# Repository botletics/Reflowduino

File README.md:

# Reflowduino

## Introduction
First off, let's briefly explain a circuit board is assembled. To aid in the explanation, let's take the analogy of baking a pizza. First of all you'll need the crust, which for us is a bare printed circuit board (PCB) made with different layers of a plastic substrate and copper traces that make the electrical connections. Next, we'll need the cheese that holds everything together, which for us is solder paste (yes, solder in the form of a paste) which "reflows" (solidifies or cures) at a high temperature. The solder paste is applied to the exposed copper pads on the PCB by way of a stencil that is aligned over the PCB. Then we'll grab some toppings, the electrical components, and place them in their appropriate locations on top of the solder paste. The final step is to bake our "pizza" so that the "cheese" holds all the components in place to yield our final assembled board! This is where the Reflowduino project comes in...

## Overview
The Reflowduino project is an entire do-it-yourself (DIY) reflow ecosystem consisting of open-source hardware specifically built to make it easy to control reflow appliances and apply PID temperature control while maintaining full flexibility in programming and usage while offering a bunch of features.

Since I'm a firm believer of great online resources having learned everything on my own aside from my Mechanical Engineering degree, I'm sharing all of this as completely open-source for everyone to enjoy, including EAGLE PCB files, Arduino IDE example code, sample Android app for Bluetooth control, and full tutorials on how to modify a toaster oven to start cookin’!

That being said, I do offer the boards listed below [for sale on my website](https://www.botletics.com/products/). Each order helps me out a little bit in creating and sharing new projects with everyone! :)

## Resources
Don’t forget to check out the [comprehensive Github wiki](https://github.com/botletics/Reflowdiuno/wiki)!
I also posted [this Instructable](https://www.instructables.com/id/Reflowduino-DIY-BLE-Reflow-Oven-Controller/) as a quick 'n dirty summary of everything here as well as on [Hackster.io](https://www.hackster.io/botletics/diy-reflow-oven-with-reflowduino-af0219)!

All PCB design files and hardware are released under the [Creative Commons Attribution Share Alike 4.0](https://choosealicense.com/licenses/cc-by-sa-4.0/) license.

All other software is released under the [GNU General Public License v3.0](https://choosealicense.com/licenses/gpl-3.0/).

## Safety Disclaimer
If you are a beginner in electronics or don't have the proper experience to work with mains voltage, I would suggest that you either don't mess with it, consult a professional, or keep learning until you're proficient enough! I am not liable for any mishaps that may occur due to misuse of the Reflowduino or its associated components or electrical system (including mains power). Take all safety precautions as necessary, such as gloves and certified safety glasses. Moreover, it is not recommended that you use the same appliance to reflow PCB's and also to cook food for consumption, which may result in food poisoning, especially with leaded solder. You are fully responsible for your actions, and perform them at your own risk!

That being said, DIY away my friends... have fun and stay safe!

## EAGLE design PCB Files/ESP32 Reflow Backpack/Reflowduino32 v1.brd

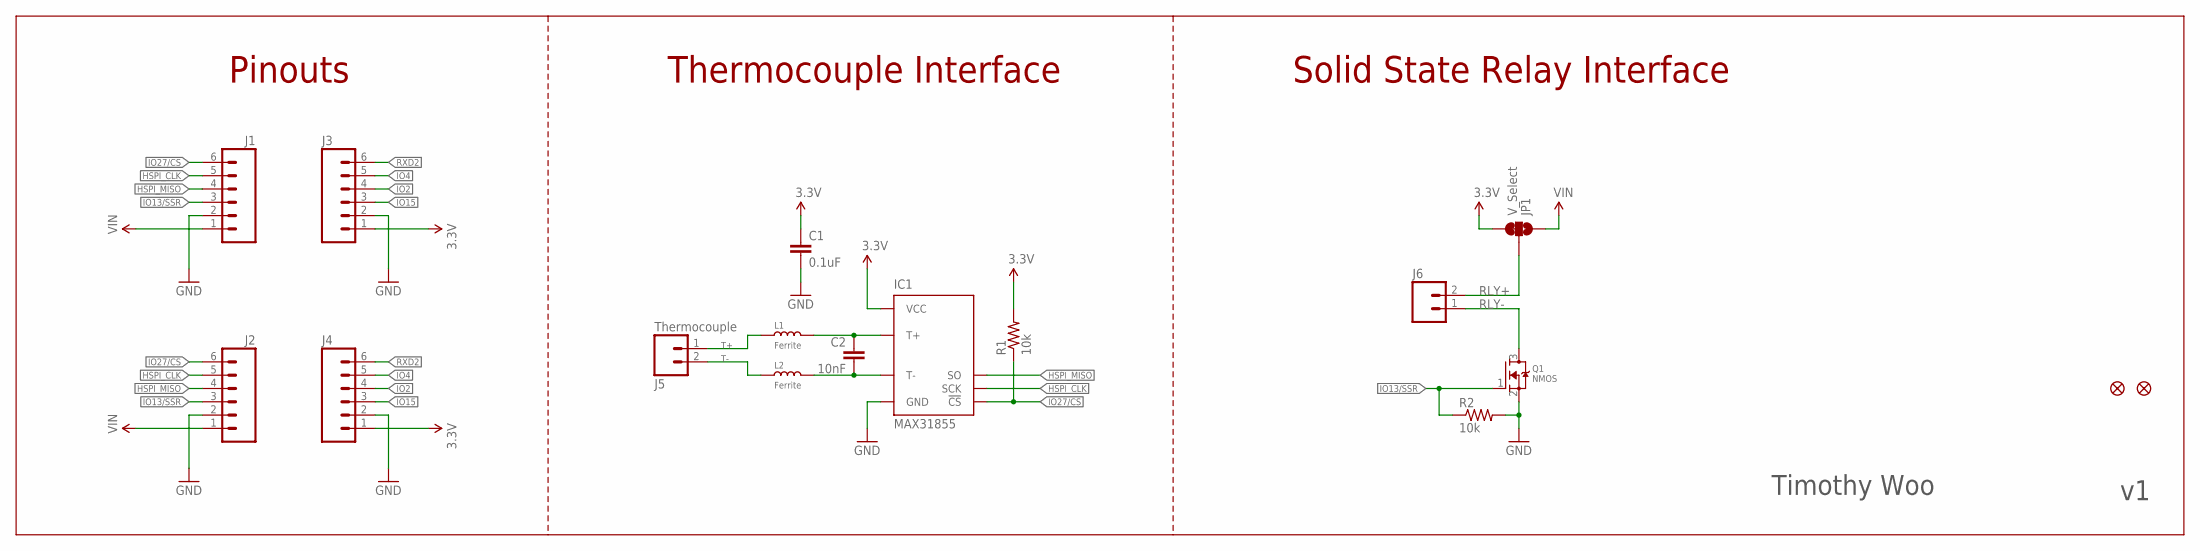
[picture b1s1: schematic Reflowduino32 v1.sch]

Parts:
C1: 0.1uF; 0603-CAP-MARKED
C2: 10nF; 0603-CAP-MARKED
FID1, FID2: FIDUCIAL; FIDUCIAL_1MM
IC1: MAX31855; MAX31855_SOIC8
J1, J3: M06SILK_PTH; 1X06
J2, J4: M06NO_SILK_FEMALE_PTH; 1X06_NO_SILK
J5: Thermocouple; SCREWTERMINAL-3.5MM-2
J6: M023.5MM; SCREWTERMINAL-3.5MM-2
JP1: V_Select; SMT-JUMPER_3_1-NC_TRACE_SILK
L1, L2: Ferrite; L0603
Q1: NMOS; SOT23-3
R1, R2: 10k; 0603-RES-MARKED

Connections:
3.3V: C1.1, IC1.4 (VCC), J3.1, J4.1, JP1.3, R1.2
GND: C1.2, IC1.1 (GND), J1.2, J2.2, J3.2, J4.2, Q1.2 (S), R2.2
HSPI_CLK: IC1.5 (SCK), J1.5, J2.5
HSPI_MISO: IC1.7 (SO), J1.4, J2.4
IO2: J3.4, J4.4
IO4: J3.5, J4.5
IO13/SSR: J1.3, J2.3, Q1.1 (G), R2.1
IO15: J3.3, J4.3
IO27/CS: IC1.6 (!CS), J1.6, J2.6, R1.1
unnamed: C2.2, IC1.2 (T-), L2.2
unnamed: C2.1, IC1.3 (T+), L1.2
RLY+: J6.2, JP1.2
RLY-: J6.1, Q1.3 (D)
RXD2: J3.6, J4.6
T+: J5.1, L1.1
T-: J5.2, L2.1
VIN: J1.1, J2.1, JP1.1

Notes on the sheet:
Thermocouple Interface
Solid State Relay Interface
Pinouts
Timothy Woo

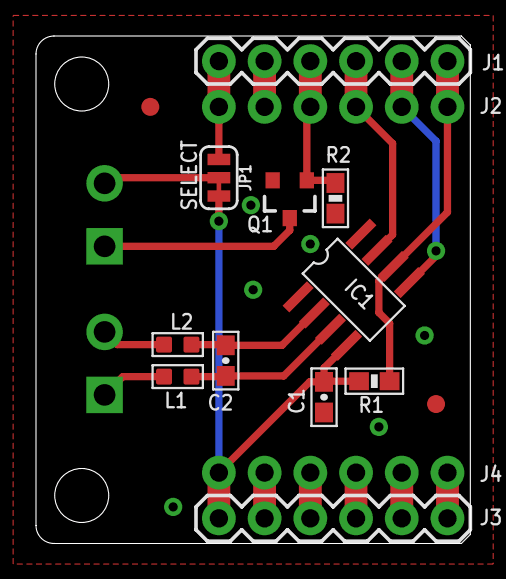
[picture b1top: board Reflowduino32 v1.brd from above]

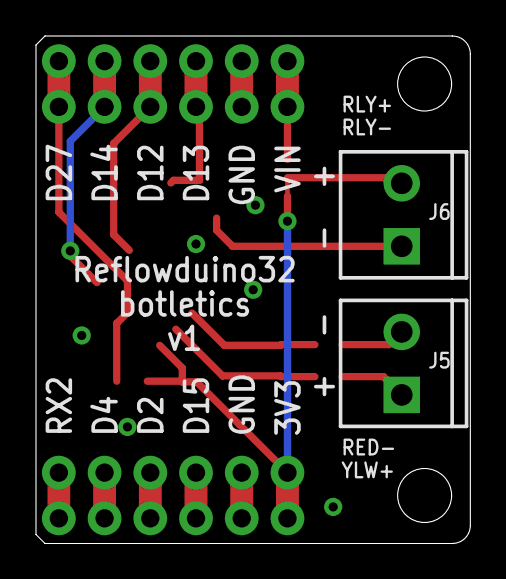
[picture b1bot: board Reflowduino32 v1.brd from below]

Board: 2 copper layers, 24.1 x 28.2 mm, 17 parts (2 on the bottom side), 17 nets.

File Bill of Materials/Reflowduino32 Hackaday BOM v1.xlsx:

Part # | Part Name | Quantity | Notes | Mfg. Number
C1 | 0.1uF/16V/20%/X7R Ceramic Capacitor 0603 | 1 |  | CL10B104MO8NNND
C2 | 0.01uF/16V/10%/X7R Ceramic Capacitor 0603 | 1 |  | CL10B103KO8NNNC
IC1 | MAX31855 Thermocouple-to-Digital Converter | 1 | K-type | MAX31855KASA+
J1, J3 | 1x6 Female Header, 2.54mm Pitch/8.5mm Tall | 2
J5-J6 | 2-pin Screw Terminal Block, 3.5mm Pitch | 2 |  | T502015000J0G
L1-L2 | 600Ohm Ferrite Bead, Signal Filter, 0603 | 2 |  | BLM18TG601TN1D
Q1 | N-MOSFET, 200mA, SOT23-3 | 1 | Very low Vth | BSS138L
R1-R2 | 10k/5%/0.1W Resistor 0603 | 2 |  | NRC06J103TRF

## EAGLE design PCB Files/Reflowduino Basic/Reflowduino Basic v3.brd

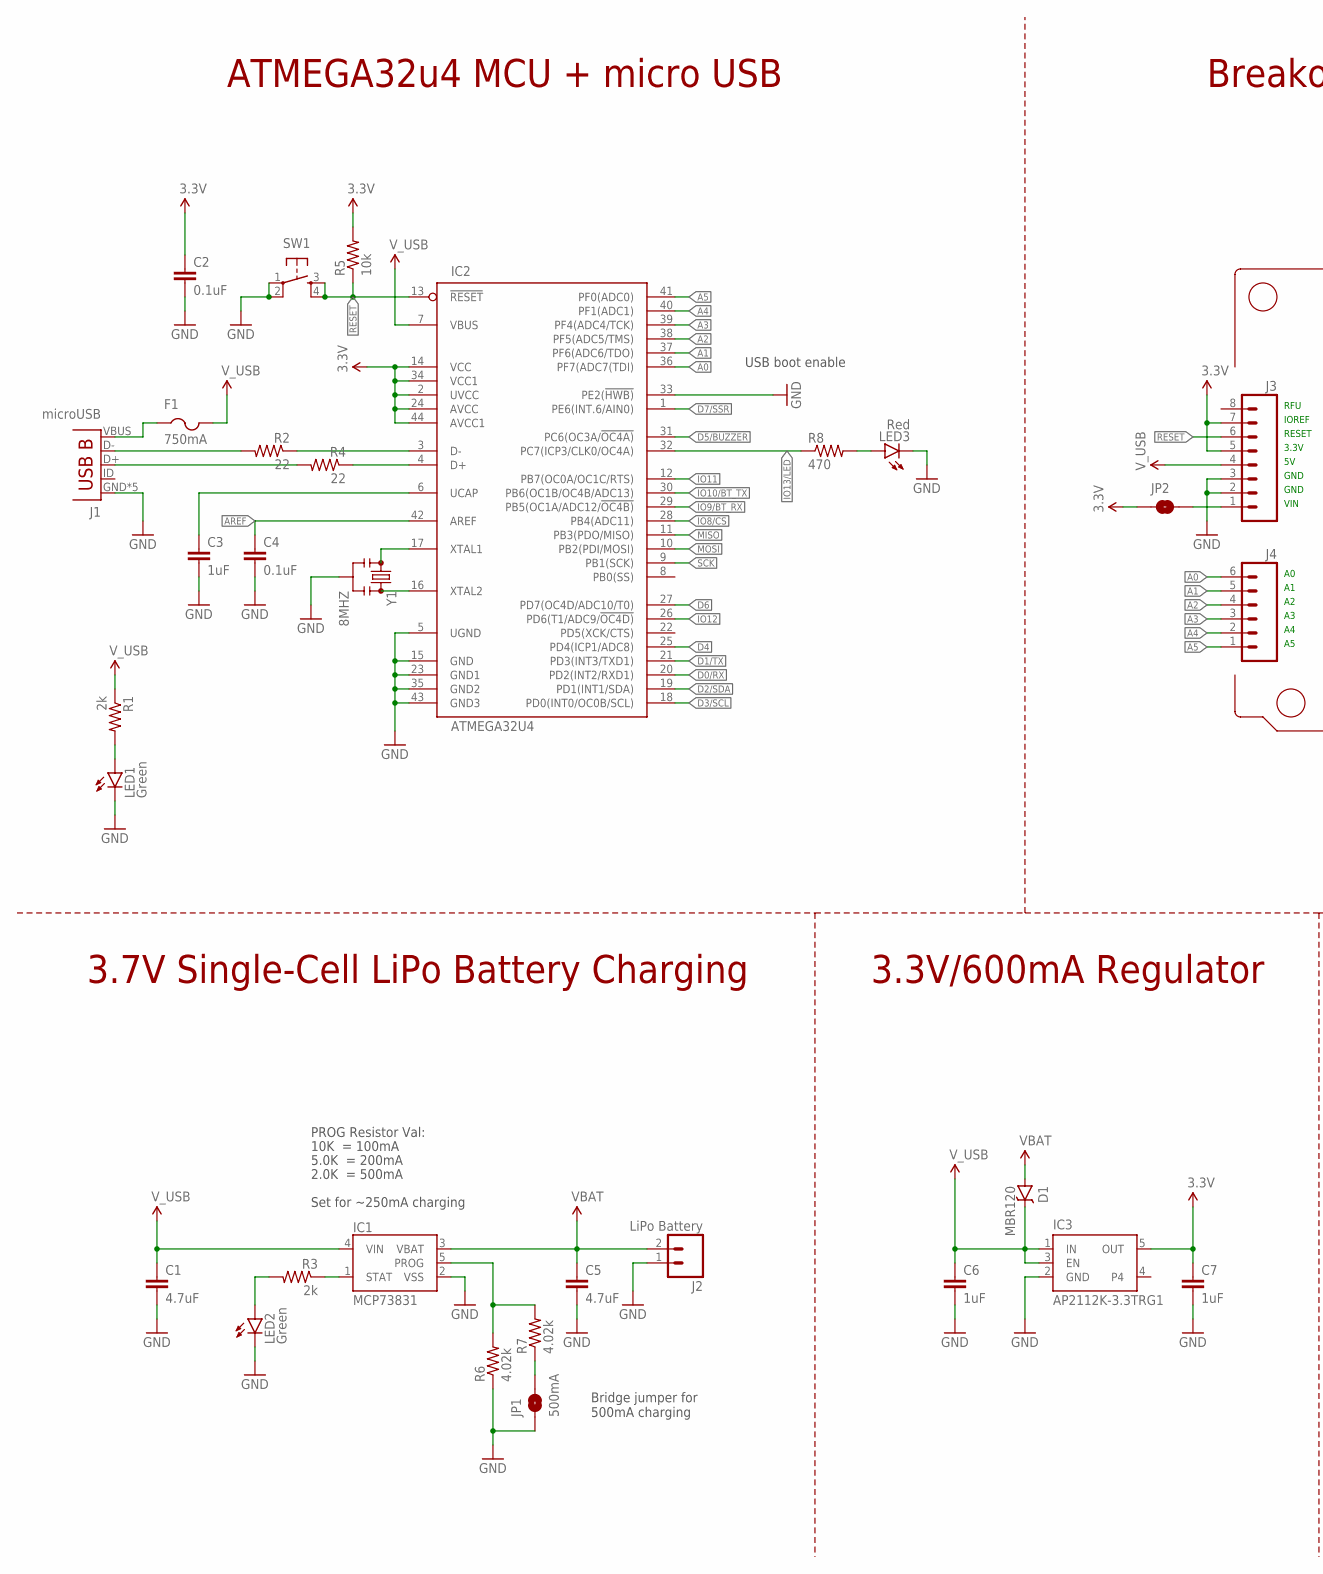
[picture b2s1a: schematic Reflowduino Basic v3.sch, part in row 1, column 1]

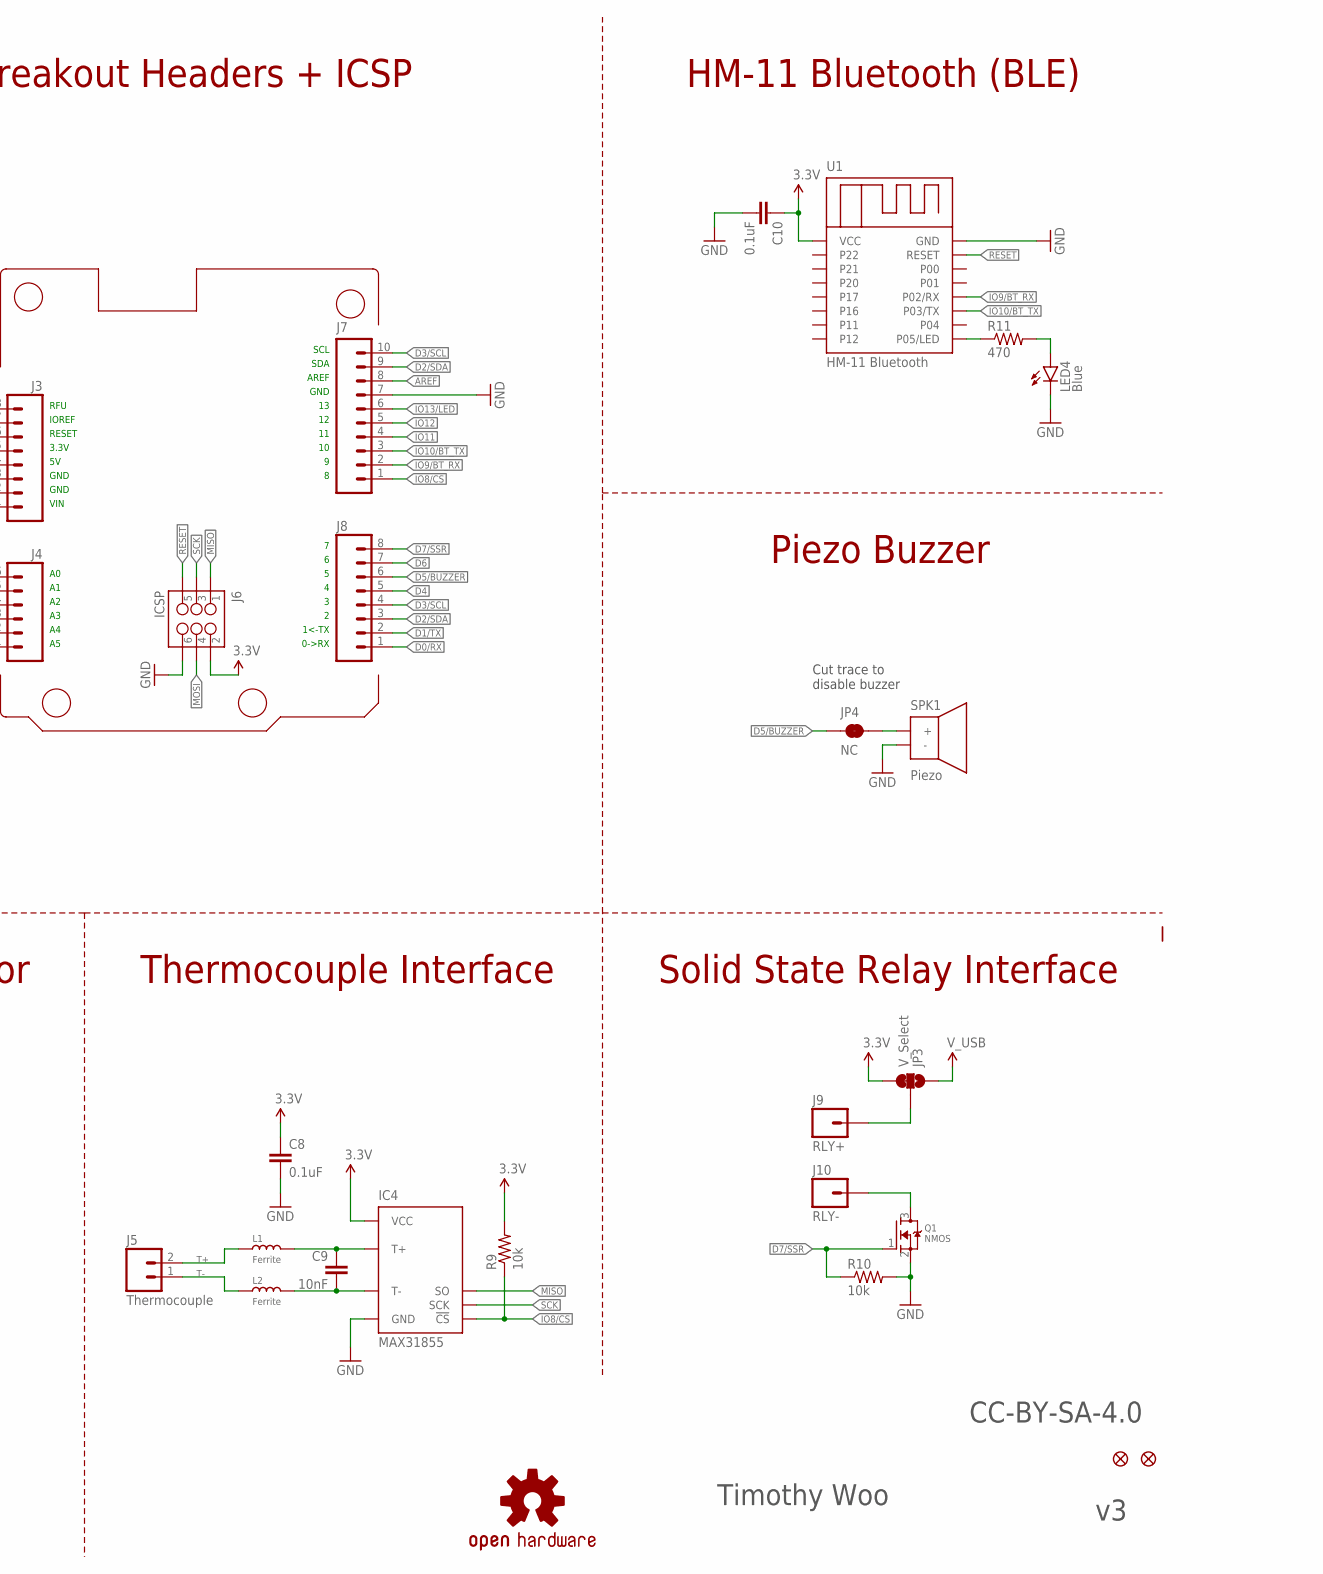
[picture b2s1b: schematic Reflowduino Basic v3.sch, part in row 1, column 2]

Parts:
C1, C5: 4.7uF; 0603-CAP-MARKED
C2, C4, C8, C10: 0.1uF; 0603-CAP-MARKED
C3, C6, C7: 1uF; 0603-CAP-MARKED
C9: 10nF; 0603-CAP-MARKED
D1: MBR120; SOD-123FL
F1: 750mA; 1210
FID1, FID2: FIDUCIAL; FIDUCIAL_1MM
IC1: MCP73831; SOT23-5
IC2: ATMEGA32U4; TQFP44
IC3: AP2112K-3.3TRG1; SOT23-5
IC4: MAX31855; MAX31855_SOIC8
J1: microUSB; USB-B-MICRO-SMD
J2: LiPo Battery; JST-2-SMD
J3, J8: M08SILK_PTH; 1X08
J4: M06SILK_PTH; 1X06
J5: Thermocouple; SCREWTERMINAL-3.5MM-2
J6: ICSP; 2X3
J7: M10SILK_PTH; 1X10
J9: RLY+; 1X01_LONGPAD
J10: RLY-; 1X01_LONGPAD
JP1: 500mA; SMT-JUMPER_2_NO_SILK
JP2: JUMPER-SMT_2_NO_SILK; SMT-JUMPER_2_NO_SILK
JP3: V_Select; SMT-JUMPER_3_1-NC_TRACE_SILK
JP4: NC; SMT-JUMPER_2_NC_TRACE_SILK
L1, L2: Ferrite; L0603
LED1, LED2: Green; LED-0603-MARKED
LED3: Red; LED-0603-MARKED
LED4: Blue; LED-0603-MARKED
LOGO1: OSHW-LOGOL; OSHW-LOGO-L
Q1: NMOS; SOT23-3
R1, R3: 2k; 0603-RES-MARKED
R2, R4: 22; 0603-RES-MARKED
R5, R9, R10: 10k; 0603-RES-MARKED
R6, R7: 4.02k; 0603-RES-MARKED
R8, R11: 470; 0603-RES-MARKED
SPK1: Piezo; BUZZER_PKMCS0909E4000
SW1: SWITCH_MOMENTARY_SPST_4-PINRECT; TACTILE_SWITCH_SMD_4.6X2.8MM
U1: HM-11 Bluetooth; JDY-08_BLUETOOTH
Y1: 8MHZ; CSTCE_RESONATOR_SMD

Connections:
3.3V: C2.1, C7.1, C8.1, C10.1, IC2.2 (UVCC), IC2.14 (VCC), IC2.24 (AVCC), IC2.34 (VCC1), IC2.44 (AVCC1), IC3.5 (OUT), IC4.4 (VCC), J3.5, J3.7, J6.2, JP2.1, JP3.3, R5.2, R9.2, U1.1 (VCC)
A0: IC2.36 (PF7(ADC7(TDI)), J4.6
A1: IC2.37 (PF6(ADC6/TDO)), J4.5
A2: IC2.38 (PF5(ADC5/TMS)), J4.4
A3: IC2.39 (PF4(ADC4/TCK)), J4.3
A4: IC2.40 (PF1(ADC1)), J4.2
A5: IC2.41 (PF0(ADC0)), J4.1
AREF: C4.1, IC2.42 (AREF), J7.8
D0/RX: IC2.20 (PD2(INT2/RXD1)), J8.1
D1/TX: IC2.21 (PD3(INT3/TXD1)), J8.2
D2/SDA: IC2.19 (PD1(INT1/SDA)), J7.9, J8.3
D3/SCL: IC2.18 (PD0(INT0/OC0B/SCL)), J7.10, J8.4
D4: IC2.25 (PD4(ICP1/ADC8)), J8.5
D5/BUZZER: IC2.31 (PC6(OC3A/!OC4A)), J8.6, JP4.1
D6: IC2.27 (PD7(OC4D/ADC10/T0)), J8.7
D7/SSR: IC2.1 (PE6(INT.6/AIN0)), J8.8, Q1.1 (G), R10.1
D+: IC2.4 (D+), R4.1
D-: IC2.3 (D-), R2.1
DC+: J9.1, JP3.2
DC-: J10.1, Q1.3 (D)
GND: C1.2, C2.2, C3.2, C4.2, C5.2, C6.2, C7.2, C8.2, C10.2, IC1.2 (VSS), IC2.5 (UGND), IC2.15 (GND), IC2.23 (GND1), IC2.33 (PE2(!HWB)), IC2.35 (GND2), IC2.43 (GND3), IC3.2 (GND), IC4.1 (GND), J1.GND, J1.SHIELD1 (GND), J1.SHIELD2 (GND), J1.SHIELD3 (GND), J1.SHIELD4 (GND), J2.1 (2), J3.2, J3.3, J6.6, J7.7, JP1.1, LED1.C, LED2.C, LED3.C, LED4.C, Q1.2 (S), R6.1, R10.2, SPK1.2 (-), SW1.1, SW1.2, U1.16 (GND), Y1.2
IO8/CS: IC2.28 (PB4(ADC11)), IC4.6 (!CS), J7.1, R9.1
IO9/BT_RX: IC2.29 (PB5(OC1A/ADC12/!OC4B)), J7.2, U1.12 (P02/RX)
IO10/BT_TX: IC2.30 (PB6(OC1B/OC4B/ADC13)), J7.3, U1.11 (P03/TX)
IO11: IC2.12 (PB7(OC0A/OC1C/RTS)), J7.4
IO12: IC2.26 (PD6(T1/ADC9/!OC4D)), J7.5
IO13/LED: IC2.32 (PC7(ICP3/CLK0/OC4A)), J7.6, R8.1
LED: R11.1, U1.9 (P05/LED)
MISO: IC2.11 (PB3(PDO/MISO)), IC4.7 (SO), J6.1
MOSI: IC2.10 (PB2(PDI/MOSI)), J6.4
unnamed: IC2.17 (XTAL1), Y1.1
unnamed: J1.D-, R2.2
unnamed: J1.D+, R4.2
unnamed: JP4.2, SPK1.1 (+)
unnamed: LED2.A, R3.2
unnamed: C9.2, IC4.2 (T-), L2.2
unnamed: C9.1, IC4.3 (T+), L1.2
unnamed: LED1.A, R1.2
unnamed: IC2.16 (XTAL2), Y1.3
unnamed: LED4.A, R11.2
unnamed: JP1.2, R7.1
unnamed: J3.1, JP2.2
unnamed: LED3.A, R8.2
PROG: IC1.5 (PROG), R6.2, R7.2
RESET: IC2.13 (!RESET), J3.6, J6.5, R5.1, SW1.3, SW1.4, U1.15 (RESET)
SCK: IC2.9 (PB1(SCK)), IC4.5 (SCK), J6.3
STAT: IC1.1 (STAT), R3.1
T+: J5.2, L1.1
T-: J5.1, L2.1
UCAP: C3.1, IC2.6 (UCAP)
VBAT: C5.1, D1.A, IC1.3 (VBAT), J2.2 (1)
V_USB: C1.1, C6.1, D1.C, F1.2, IC1.4 (VIN), IC2.7 (VBUS), IC3.1 (IN), IC3.3 (EN), J3.4, JP3.1, R1.1
XUSB: F1.1, J1.VBUS

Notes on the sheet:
Timothy Woo
IOREF
RFU
3.3V
RESET
GND
VIN
0->RX
1<-TX
AREF
SDA
SCL
Set for ~250mA charging
10K = 100mA
5.0K = 200mA
2.0K = 500mA
PROG Resistor Val:
ATMEGA32u4 MCU + micro USB
3.7V Single-Cell LiPo Battery Charging
3.3V/600mA Regulator
Breakout Headers + ICSP
HM-11 Bluetooth (BLE)
Solid State Relay Interface
Thermocouple Interface
Piezo Buzzer
Bridge jumper for 500mA charging
Cut trace to disable buzzer
USB boot enable
CC-BY-SA-4.0

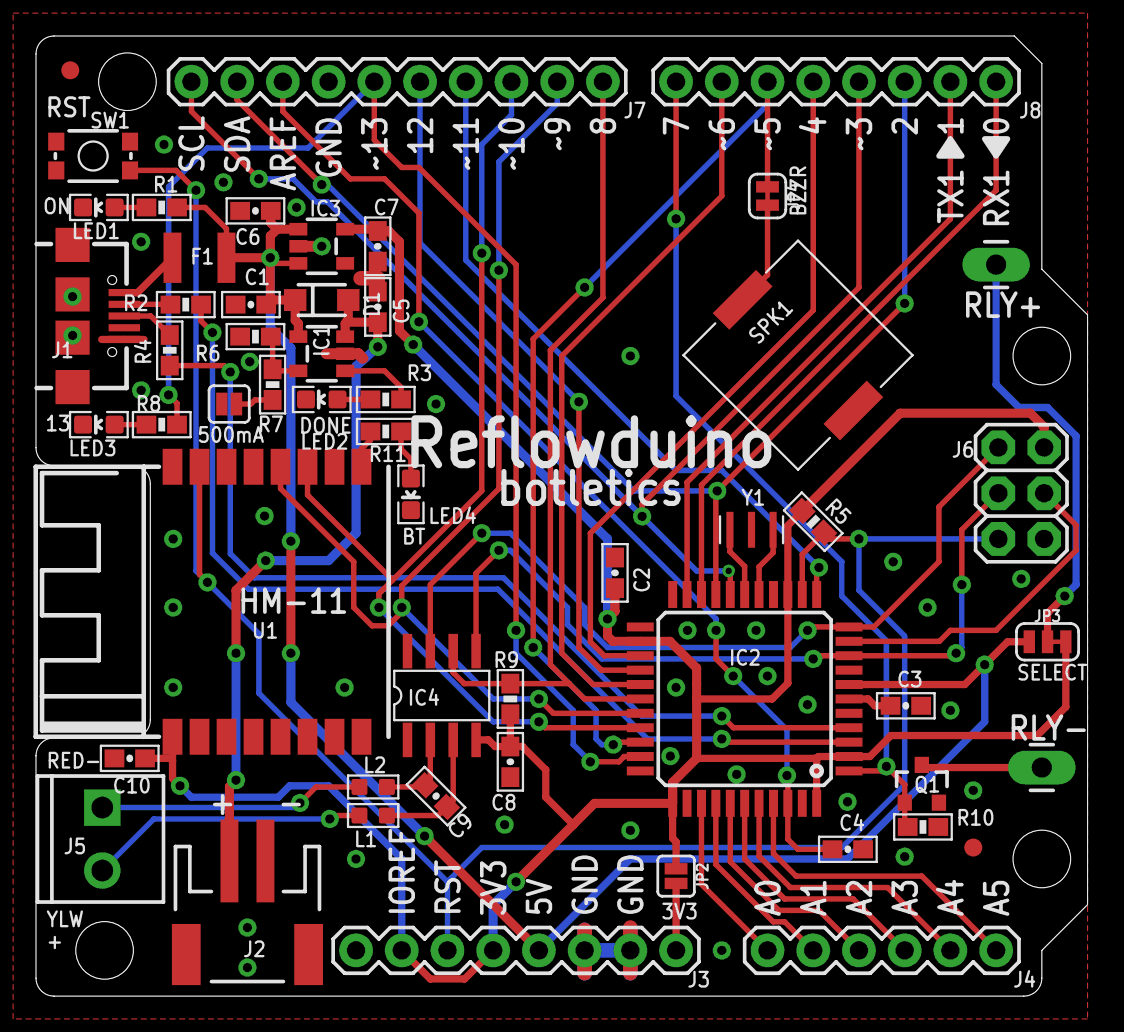
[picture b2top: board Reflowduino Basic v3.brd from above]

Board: 2 copper layers, 58.4 x 53.3 mm, 55 parts (1 on the bottom side), 53 nets.

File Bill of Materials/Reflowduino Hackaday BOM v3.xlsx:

Part # | Part Description | Quantity | Notes | Mfg. Number
C1, C5 | 4.7uF/6.3V/10%/X5R Ceramic Capacitor 0603 | 2 |  | CL10A475KQ8NNNL
C2,C4,C8,C10 | 0.1uF/16V/20%/X7R Ceramic Capacitor 0603 | 4 |  | CL10B104MO8NNND
C3, C6, C7 | 1uF/25V/10%/X5R Ceramic Capacitor, 0603 | 3 |  | CL10A105KA8NNLC
C9 | 0.01uF/16V/10%/X7R Ceramic Capacitor 0603 | 1 |  | CL10B103KO8NNNC
D1 | Schottky Diode, 20V/1A, SOD-123FL | 1 |  | MBR120VLSFT3G
F1 | PTC Resettable Fuse, 750mA | 1 | 1210 package | 0ZCH0075AF2E
IC1 | Single Cell Li-Ion Charger IC, SOT23-5 | 1 |  | MCP73831T-2ACIOT
IC2 | ATMEGA32U4RC-AU, 44TQFP (10x10) | 1 | Internal calib. RC | ATMEGA32U4RC-AU
IC3 | 3.3V/600mA Regulator, SOT23-5 | 1 |  | AP2112K-3.3TRG1
IC4 | MAX31855 Thermocouple-to-Digital Converter | 1 | K-type | MAX31855KASA+
J1 | Micro USB Connector, SMT with Alignment Pins | 1
J2 | 2mm JST-PH SMT RA Connector | 1 |  | S2B-PH-SM4-TB(LF)(SN)
J3, J8 | 1x8 Female Header, 2.54mm Pitch/8.5mm Tall | 2
J4 | 1x6 Female Header, 2.54mm Pitch/8.5mm Tall | 1
J5 | 2-pin Screw Terminal Block, 3.5mm Pitch | 1 |  | T502015000J0G
J6 | 3x2 ICSP Male Header, 2.54mm Pitch | 1 |  | 54102-G08-00
J7 | 10x1 Female Header, 2.54mm Pitch/8.5mm Tall | 1
L1-L2 | 600Ohm Ferrite Bead, Signal Filter, 0603 | 2 |  | BLM18TG601TN1D
LED1-LED2 | 3.2V/20mA Green LED, 0603 | 2 |  | 150060GS75000
LED3 | 2V/20mA Red LED, 0603 | 1 |  | 150060RS75000
LED4 | 3.2V/20mA Blue LED, 0603 | 1 |  | 150060BS75000
Q1 | N-MOSFET, 200mA, SOT23-3 | 1 | Very low Vth | BSS138L
R1, R3 | 2k/1%/0.1W Resistor 0603 | 2 |  | ERJ-3GEYJ202V
R2, R4 | 22/5%/0.1W Resistor 0603 | 2 |  | RC1608J220CS
R5,R9,R10 | 10k/5%/0.1W Resistor 0603 | 3 |  | NRC06J103TRF
R6-R7 | 4.02k/1%/0.1W Resistor 0603 | 2 |  | RK73H1JTTD4021F
R8, R11 | 470/5%/0.1W Resistor 0603 | 2 |  | RMCF0603JT470R
RY1 | Opto-Isolated Solid State Relay | 1 | 25A/280V max | SPF240D25
SPK1 | Piezo Buzzer, 65dB | 1 |  | PKMCS0909E4000-R1
SW1 | Pushbutton Switch, SPST-NO, 300gf/2.5mm Tall | 1 |  | KMR731NGLFS
U1 | HM-11 Bluetooth SMD Module | 1
Y1 | 8MHz Resonator | 1 |  | CSTCE8M00G52-R0
 | K-type Thermocouple, Glass Braid Insulation | 1 |  | 240-080

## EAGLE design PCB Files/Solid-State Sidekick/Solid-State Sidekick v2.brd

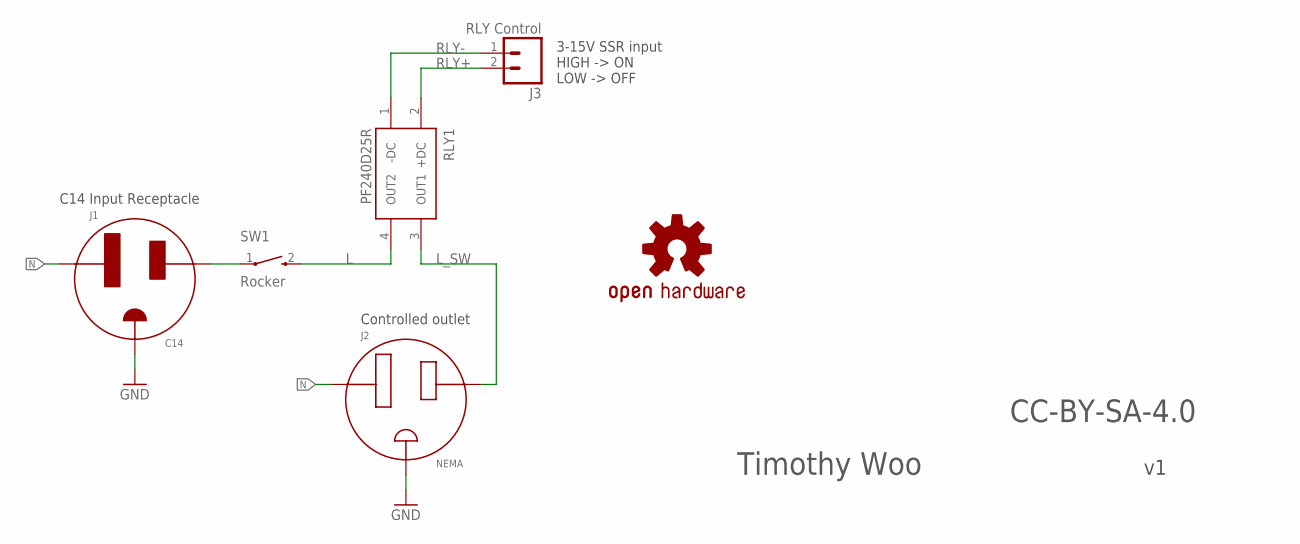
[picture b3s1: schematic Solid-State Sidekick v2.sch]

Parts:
J1: C14; 703W-00/53
J2: NEMA; 3-213598-2
J3: RLY Control; SCREWTERMINAL-3.5MM-2
LOGO1: OSHW-LOGOL; OSHW-LOGO-L
RLY1: PF240D25R; RELAY_PF240
SW1: Rocker; R1966ABLKBLKFR

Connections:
GND: J1.E, J2.GND (E)
L: RLY1.4 (OUT2), SW1.2
L_SW: J2.L, RLY1.3 (OUT1)
L_WALL: J1.L, SW1.1
N: J1.N, J2.N
RLY+: J3.2, RLY1.2 (+DC)
RLY-: J3.1, RLY1.1 (-DC)

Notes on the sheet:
Controlled outlet
3-15V SSR input HIGH -> ON LOW -> OFF
C14 Input Receptacle
Timothy Woo
CC-BY-SA-4.0

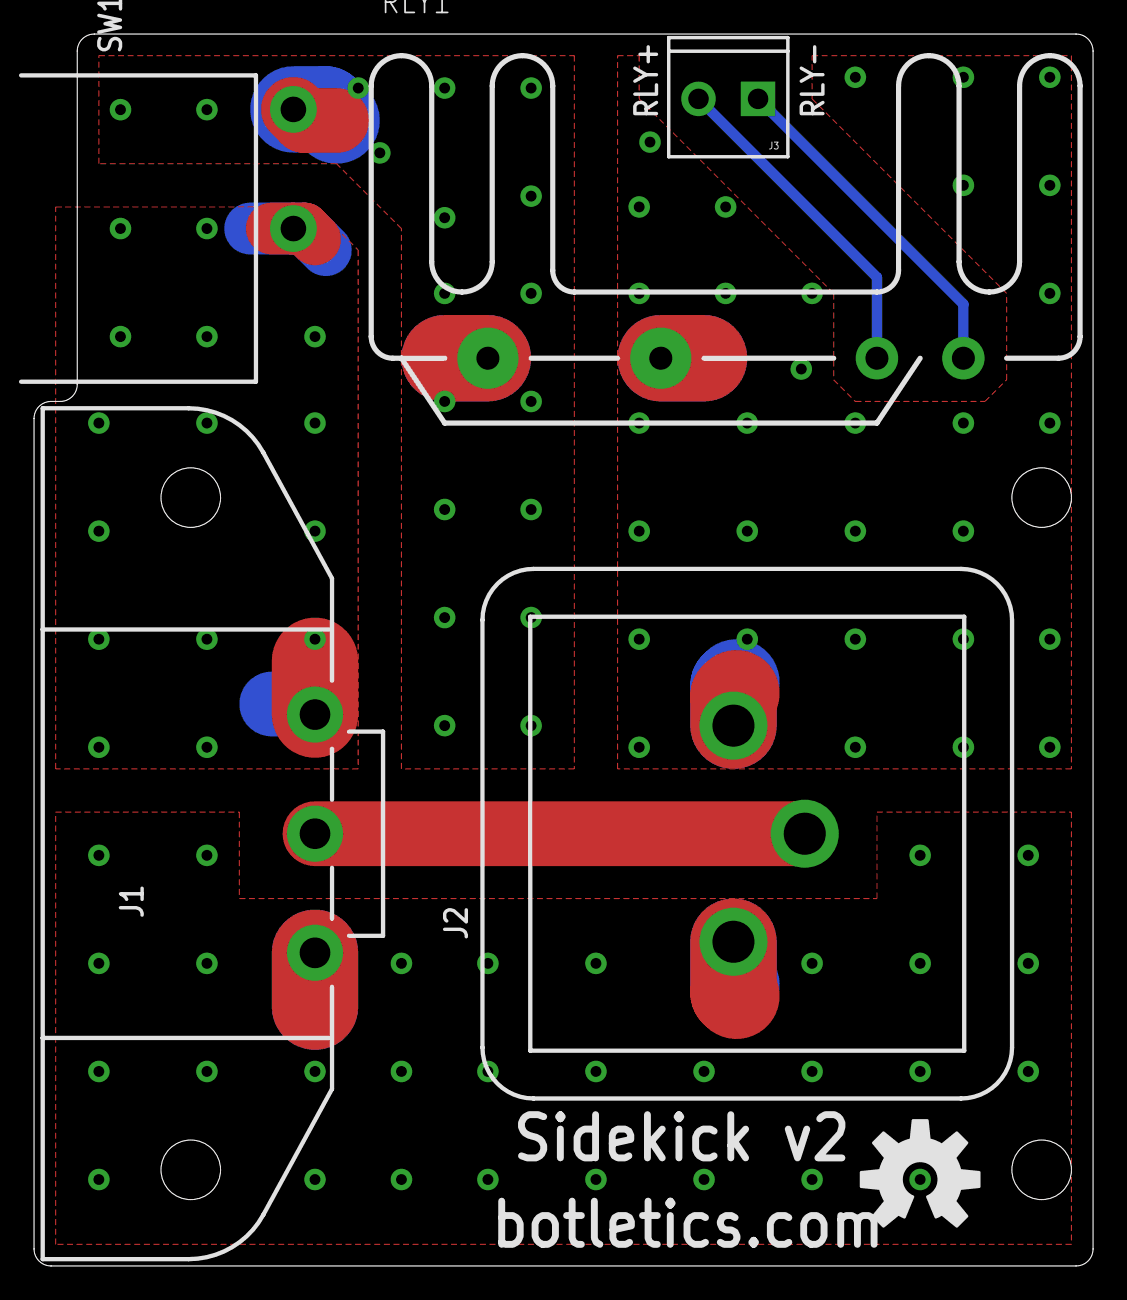
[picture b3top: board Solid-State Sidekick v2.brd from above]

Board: 2 copper layers, 62.2 x 72.4 mm, 6 parts (0 on the bottom side), 7 nets.

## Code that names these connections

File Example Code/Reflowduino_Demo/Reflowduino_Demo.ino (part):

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#include "pitches.h" // Includes the different notes for the buzzer

// Define pins
#define buzzer 5
#define relay 7
#define BT_RX 9
#define BT_TX 10
#define LED 13 // This LED is used to indicate if the reflow process is underway
#define MAX_CS 8 // MAX31855 chip select pin

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  Serial.begin(9600); // This should be different from the Bluetooth baud rate
  BT.begin(57600);

  pinMode(buzzer, OUTPUT);
  pinMode(LED, OUTPUT);
  pinMode(relay, OUTPUT);

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
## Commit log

2017-10-21 Create LICENSE
2017-11-08 Added slot isolation at relay output
2017-12-17 Bluetooth PC Code
    Talk to your Windows computer via Bluetooth!
2018-03-24 For ESP32 backpack
2018-06-07 Added serial monitor control
2018-10-17 Fixed runtime error when clicking "START"
2019-06-17 Fix temperature rate conversion error

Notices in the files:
Example Code/Reflowduino_Demo/Reflowduino_Demo.ino:
License: This code is released under the GNU General Public License v3.0
https://choosealicense.com/licenses/gpl-3.0/ and appropriate attribution must be
PCB Files/Reflowduino Basic/Reflowduino Basic v3.brd:
Released under CC-BY-SA-4.0 license
parts and their libraries:
SparkFun-Aesthetics: Licensing: Creative Commons ShareAlike 4.0 International - https://creativecommons.org/licenses/by-sa/4.0
